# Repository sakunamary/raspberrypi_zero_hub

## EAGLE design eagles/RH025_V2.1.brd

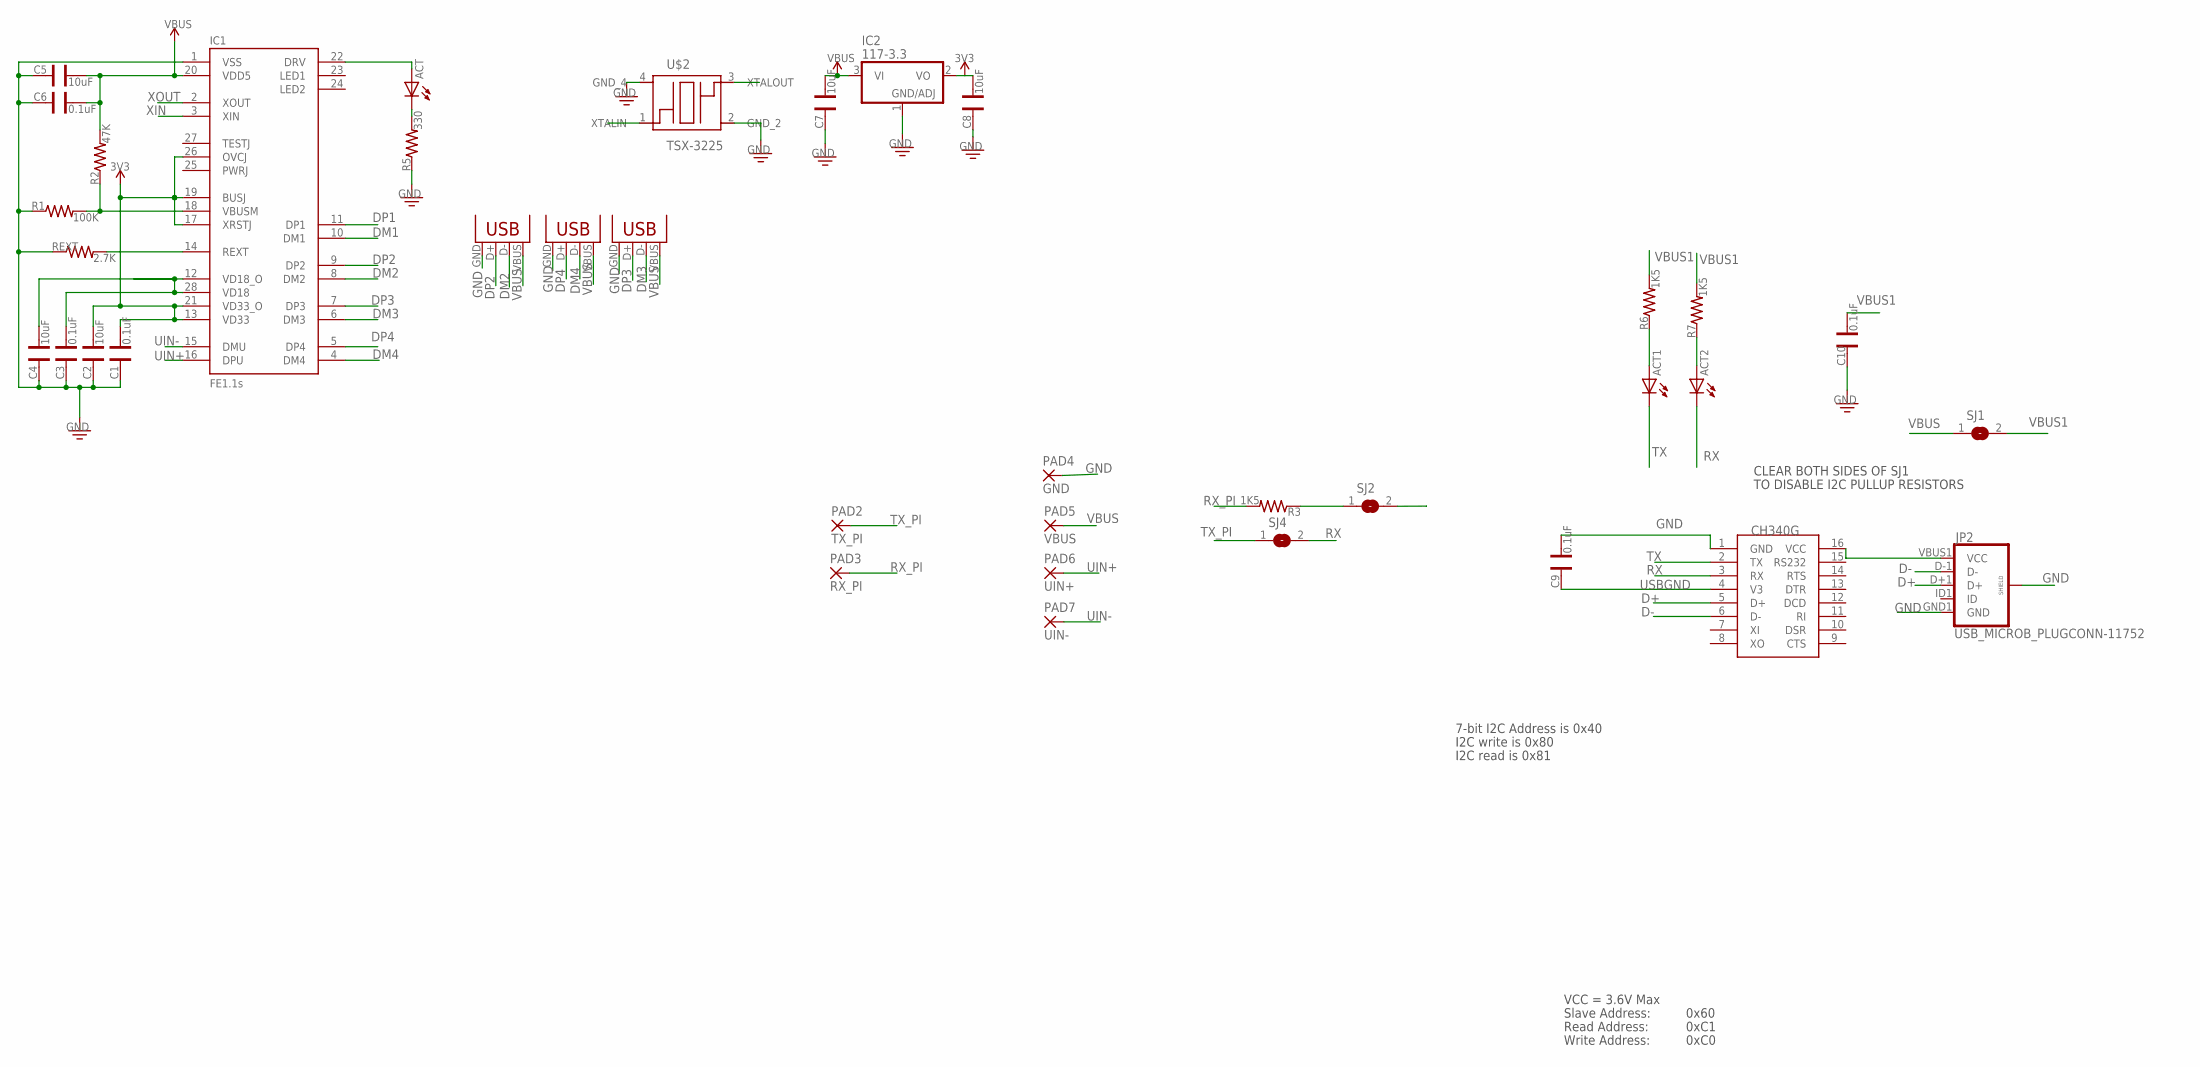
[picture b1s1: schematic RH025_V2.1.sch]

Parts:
ACT, ACT1, ACT2: LED0805; LED-0805
C1, C3, C6, C9, C10: 0.1uF; CAP-0805
C2, C4, C5, C7, C8: 10uF; CAP-0805
IC1: FE1.1S; FE1.1S_SSOP-28
IC2: 117-3.3; SOT223
JP2: USB_MICROB_PLUGCONN-11752; USB-B-MICRO-SMD_V03
PAD2: TX_PI; 2,15/1,0
PAD3: RX_PI; 2,15/1,0
PAD4: GND; 2,15/1,0
PAD5: VBUS; 2,15/1,0
PAD6: UIN+; 2,15/1,0
PAD7: UIN-; 2,15/1,0
R1: 100K; RES-0805
R2: 47K; RES-0805
R3, R6, R7: 1K5; RES-0805
R5: 330; RES-0805
REXT: 2.7K; RES-0805
SJ1, SJ2, SJ4: SJ
U$2: TSX-3225
U$8: CH340C; SOIC16
USB2, USB3, USB4: USBA-PTH; USB-A-F-PTH

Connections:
3V3: C1.1, C2.1, C8.1, IC1.13 (VD33), IC1.17 (XRSTJ), IC1.19 (BUSJ), IC1.21 (VD33_O), IC1.26 (OVCJ), IC2.2 (VO)
D+: JP2.D+1 (D+), U$8.5 (D+)
D-: JP2.D-1 (D-), U$8.6 (D-)
DM1: IC1.10 (DM1)
DM2: IC1.8 (DM2), USB2.D-
DM3: IC1.6 (DM3), USB3.D-
DM4: IC1.4 (DM4), USB4.D-
DP1: IC1.11 (DP1)
DP2: IC1.9 (DP2), USB2.D+
DP3: IC1.7 (DP3), USB3.D+
DP4: IC1.5 (DP4), USB4.D+
GND: C1.2, C2.2, C3.2, C4.2, C5.2, C6.2, C7.2, C8.2, C9.1, C10.2, IC1.1 (VSS), IC2.1 (ADJ), JP2.GND1 (GND), JP2.SHIELD1 (SHIELD), JP2.SHIELD2 (SHIELD), JP2.SHIELD3 (SHIELD), PAD4.1, R1.1, R5.1, REXT.1, U$2.2 (GND_2), U$2.4 (GND_4), U$8.1 (GND), USB2.GND, USB3.GND, USB4.GND
unnamed: IC1.14 (REXT), REXT.2
unnamed: ACT2.A, R7.1
unnamed: ACT1.A, R6.1
unnamed: R3.1, SJ2.1
unnamed: C3.1, C4.1, IC1.12 (VD18_O), IC1.28 (VD18)
unnamed: IC1.18 (VBUSM), R1.2, R2.1
unnamed: ACT.C, R5.2
unnamed: ACT.A, IC1.22 (DRV)
RX: ACT2.C, SJ4.2, U$8.3 (RX)
RX_PI: PAD3.1, R3.2
TX: ACT1.C, SJ2.2, U$8.2 (TX)
TX_PI: PAD2.1, SJ4.1
UIN+: IC1.16 (DPU), PAD6.1
UIN-: IC1.15 (DMU), PAD7.1
USBGND: C9.2, U$8.4 (V3)
VBUS: C5.1, C6.1, C7.1, IC1.20 (VDD5), IC2.3 (VI), PAD5.1, R2.2, SJ1.1, USB2.VBUS, USB3.VBUS, USB4.VBUS
VBUS1: C10.1, JP2.VBUS1 (VCC), R6.2, R7.2, SJ1.2, U$8.16 (VCC)
XIN: IC1.3 (XIN), U$2.1 (XTALIN)
XOUT: IC1.2 (XOUT), U$2.3 (XTALOUT)

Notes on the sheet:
CLEAR BOTH SIDES OF SJ1
TO DISABLE I2C PULLUP RESISTORS
7-bit I2C Address is 0x40
I2C write is 0x80
I2C read is 0x81
VCC = 3.6V Max
Read Address:
Write Address:
Slave Address:
0x60
0xC1
0xC0

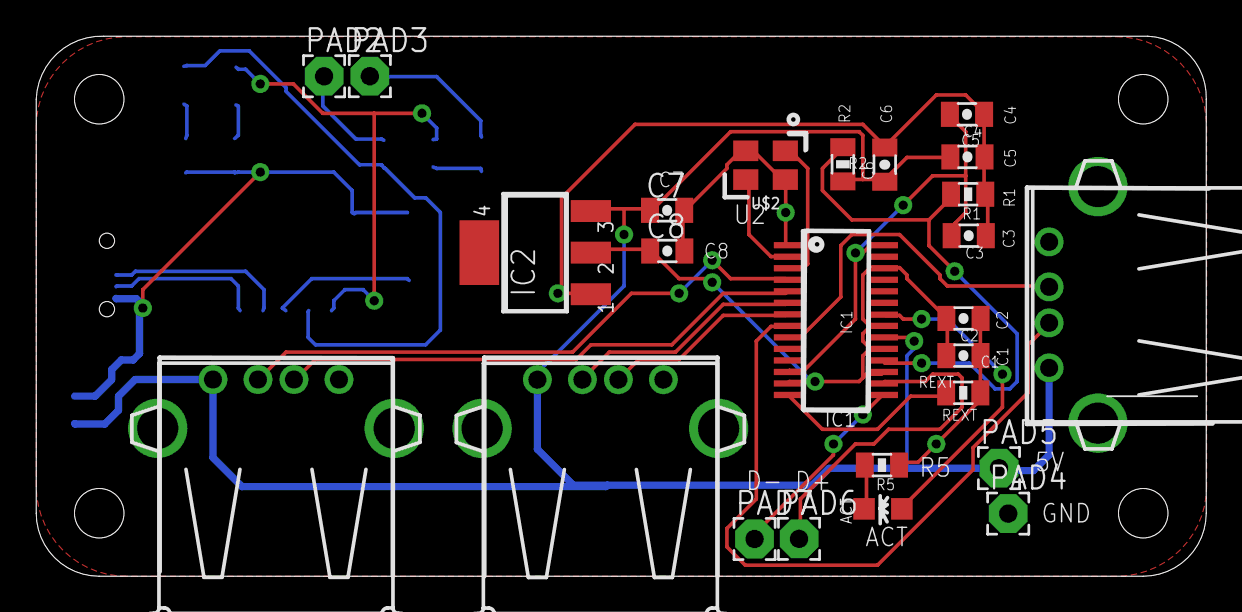
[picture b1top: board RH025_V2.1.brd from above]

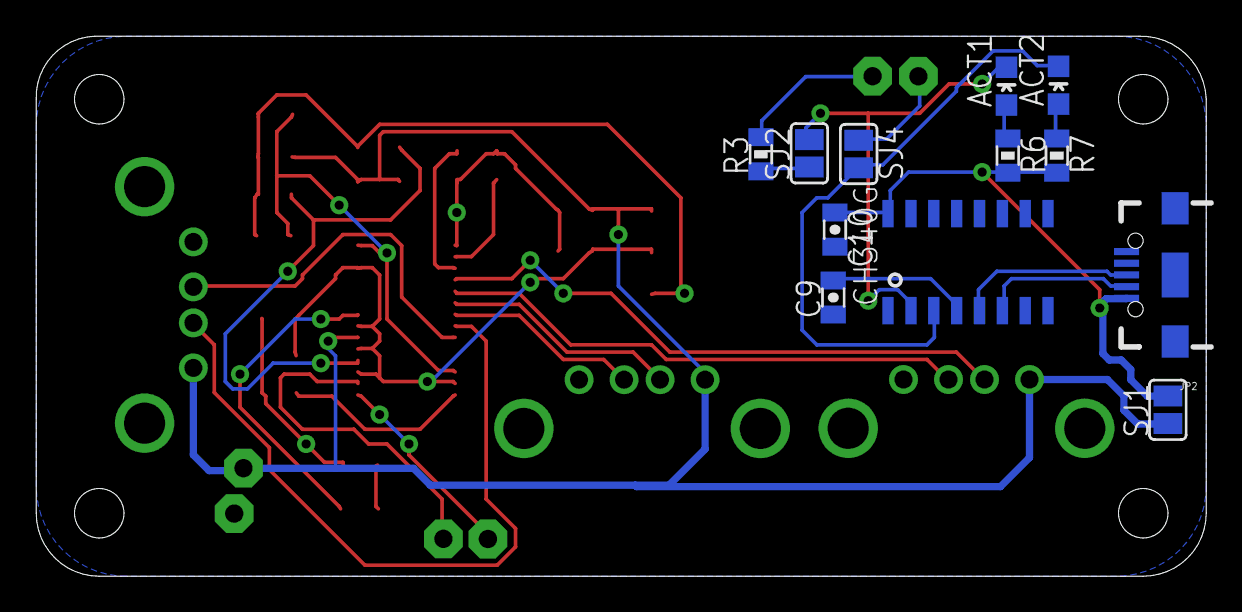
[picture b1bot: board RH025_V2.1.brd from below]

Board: 2 copper layers, 65.0 x 30.0 mm, 37 parts (12 on the bottom side), 29 nets.

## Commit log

2018-11-28 :circus_tent: Added .gitattributes & .gitignore files
2018-11-28 upload file
    upload file
2018-11-28 upload files
    upload files

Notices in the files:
parts and their libraries:
SparkFun-Connectors: Licensing: Creative Commons ShareAlike 4.0 International - https://creativecommons.org/licenses/by-sa/4.0
